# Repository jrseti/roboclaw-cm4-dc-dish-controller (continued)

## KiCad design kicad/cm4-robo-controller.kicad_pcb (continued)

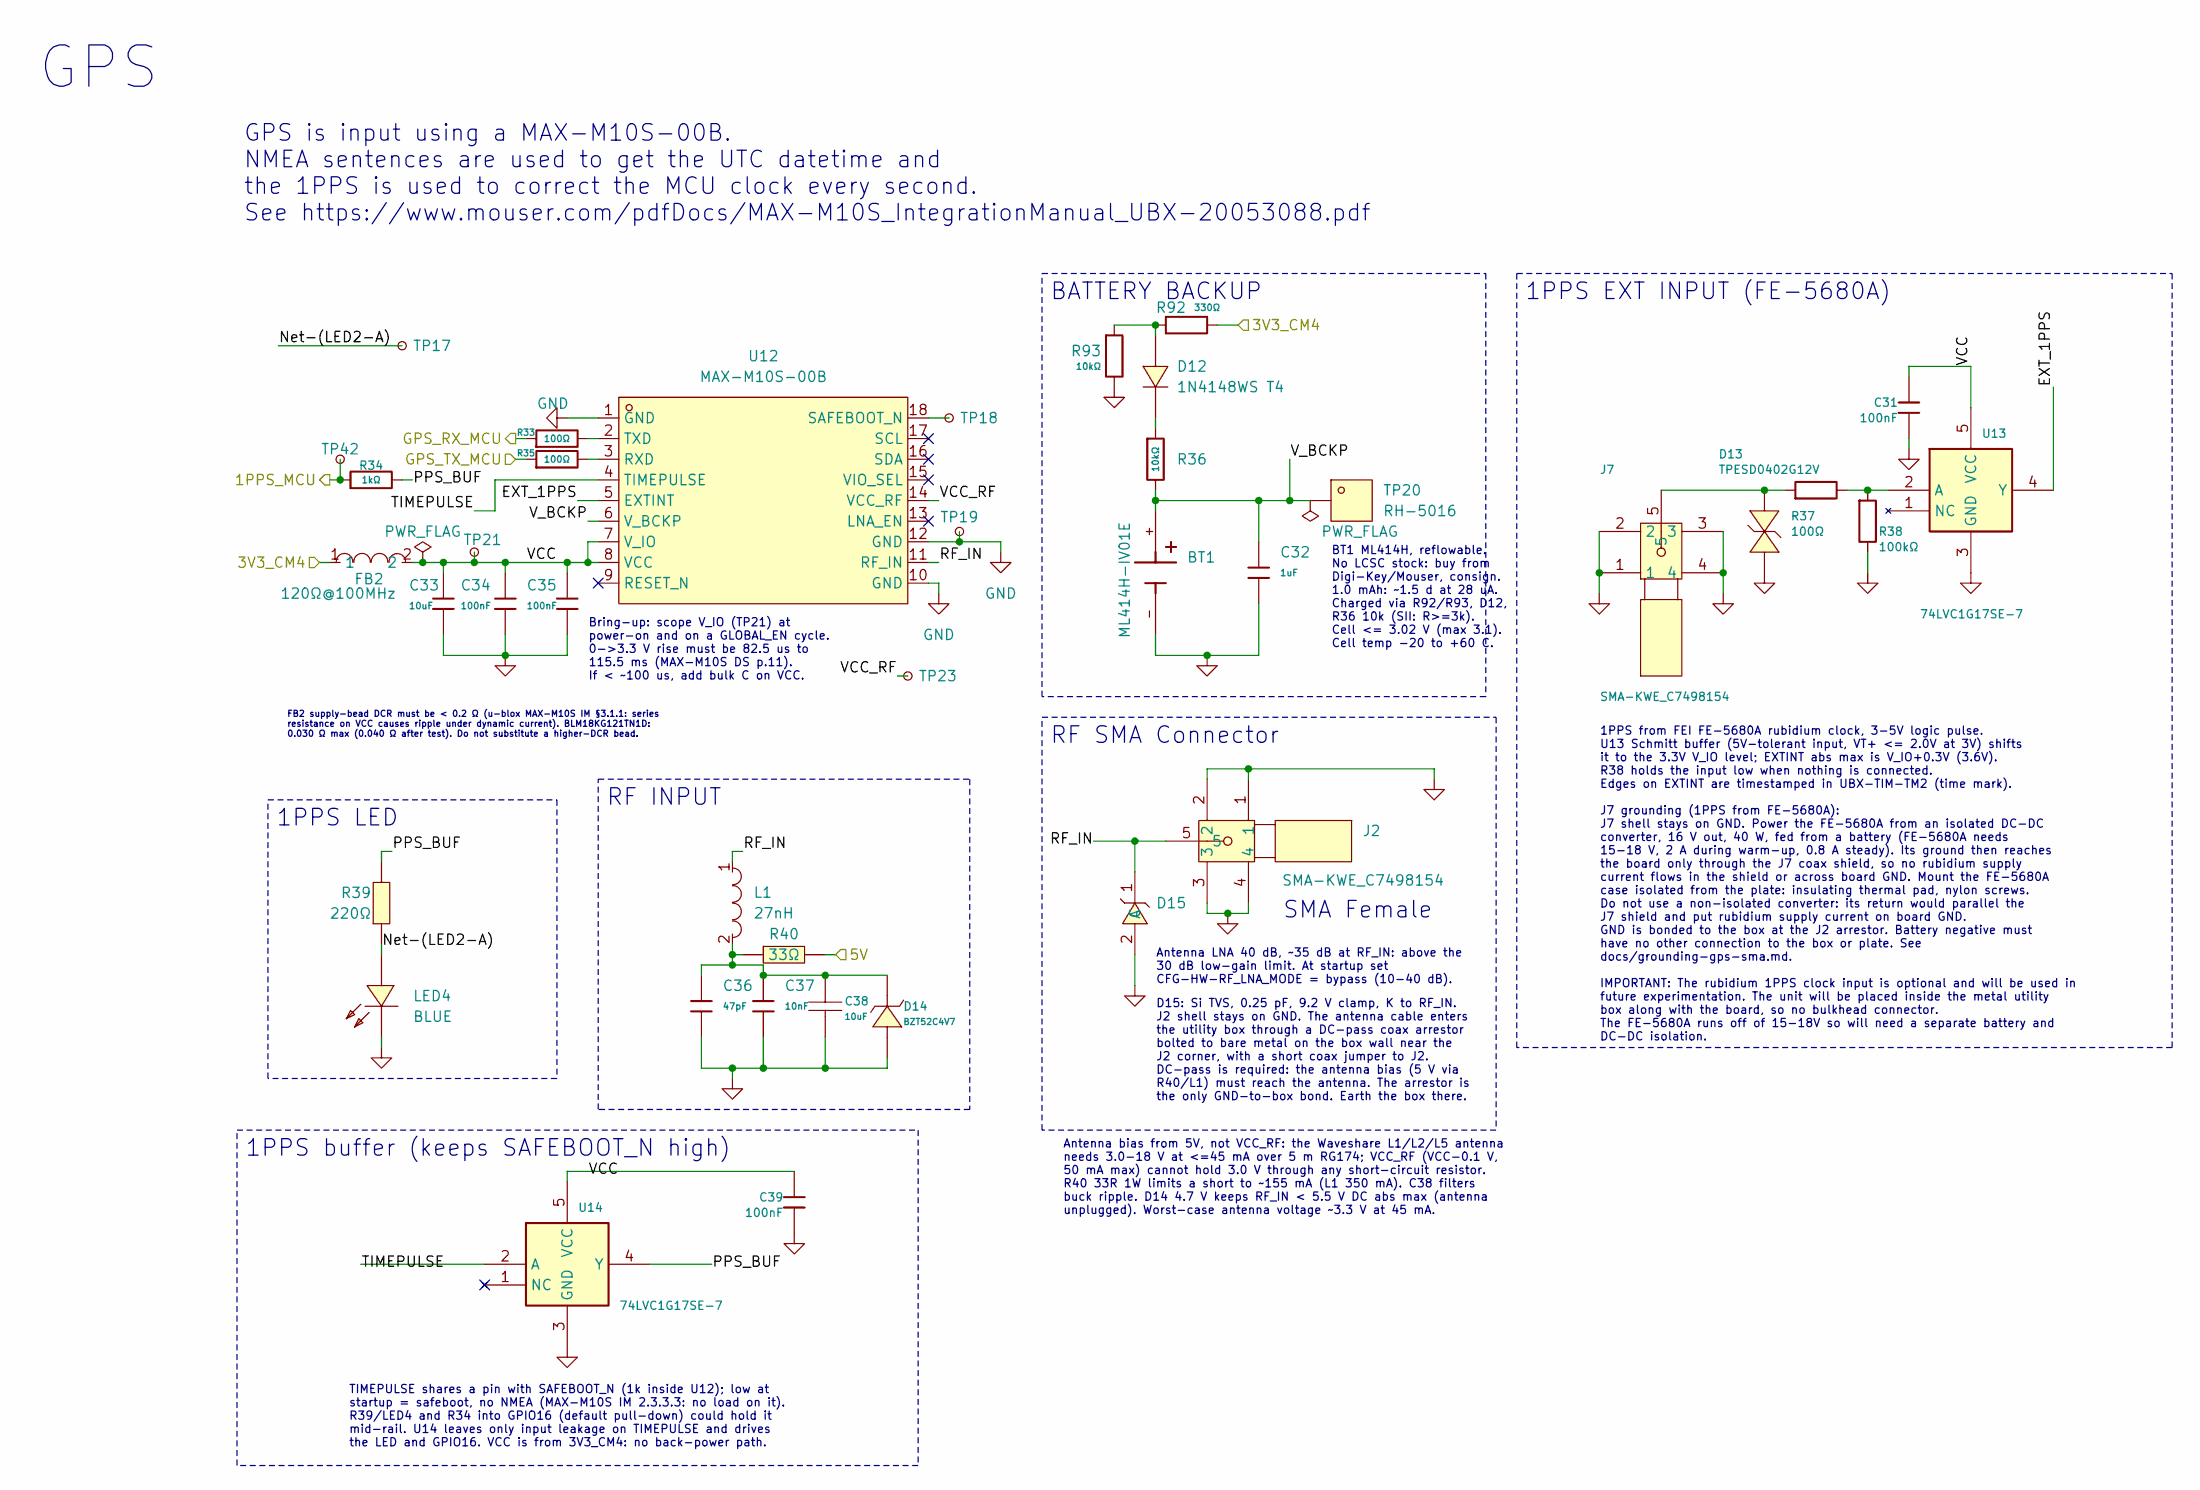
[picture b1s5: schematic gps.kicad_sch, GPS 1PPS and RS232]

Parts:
BT1: ML414H-IV01E; PARTREV E
C31, C34, C35, C39: 100nF; CAPC1608X95N; Tolerance ±10%; Voltage Rating 50V; MPN CC0603KRX7R9BB104; LCSC Part C14663
C32: 1uF; CAPC1608X95N; Tolerance ±10%; Voltage Rating 50V; MPN CL10A105KB8NNNC; LCSC Part C15849
C33: 10uF; CAPC1608X95N; Tolerance ±20%; Voltage Rating 25V; MPN CL10A106MA8NRNC; LCSC Part C96446
C36: 47pF; CAPC1608X95N; Tolerance ±5%; Voltage Rating 50V; MPN CL10C470JB8NNNC; LCSC Part C1671
C37: 10nF; CAPC1608X95N; Tolerance ±10%; Voltage Rating 50V; MPN 0603B103K500NT; LCSC Part C57112
C38: 10uF; CAPC2012X145N; Tolerance ±10%; Voltage Rating 10V; MPN CL21B106KPQNNNE; LCSC Part C32635
D12: 1N4148WS T4; SOD2513X110N; MPN 1N4148WS; LCSC Part C2128
D13: TPESD0402G12V; DIOC1005X55N; MPN TPESD0402G12V; LCSC Part C558617
D14: BZT52C4V7; SOD3716X135N; MPN BZT52C4V7; LCSC Part C19077400
D15: SESD0402X1UN-0020-090; DIOC1006X40N; MPN SESD0402X1UN-0020-090; LCSC Part C1973340
FB2: 120Ω@100MHz; INDC1608X95N; Tolerance ±25%; Current Rating 3A; MPN BLM18KG121TN1D; LCSC Part C85831
J2, J7: SMA-KWE_C7498154; SMA-TH_SMA-KWE_C7498154; MPN SMA-KWE; LCSC Part C7498154
L1: 27nH; INDC1005X55N; Tolerance ±5%; Current Rating 350mA; MPN LQG15HS27NJ02D; LCSC Part C12669
LED4: BLUE; LEDC2012X110N; MPN KT-0805B; LCSC Part C2293
R33, R35, R37: 100Ω; RESC1005X40N; Tolerance ±1%; Voltage Rating 50V; MPN 0402WGF1000TCE; LCSC Part C25076
R34: 1kΩ; RESC1005X40N; Tolerance ±1%; Voltage Rating 50V; MPN 0402WGF1001TCE; LCSC Part C11702
R36, R93: 10kΩ; RESC1608X55N; Tolerance ±1%; Voltage Rating 75V; MPN 0603WAF1002T5E; LCSC Part C25804
R38: 100kΩ; RESC1608X55N; Tolerance ±1%; Voltage Rating 75V; MPN 0603WAF1003T5E; LCSC Part C25803
R39: 220Ω; RESC1005X40N; Tolerance ±1%; Voltage Rating 50V; MPN 0402WGF2200TCE; LCSC Part C25091
R40: 33Ω; RESC6332X70N; Tolerance ±1%; Voltage Rating 200V; MPN 25121WF330JT4E; LCSC Part C53728
R92: 330Ω; RESC1608X55N; Tolerance ±1%; Voltage Rating 75V; MPN 0603WAF3300T5E; LCSC Part C23138
TP17, TP18, TP19, TP21, TP23, TP42: TestPoint_Small; TestPoint_Pad_D0.8mm
TP20: RH-5016; TESTPOINT-SMD_L3.0-W2.0; MPN RH-5016; LCSC Part C5199799
U12: MAX-M10S-00B; SMD-18_L10.1-W9.7-P1.10-TL_SKG09F; MPN MAX-M10S-00B; LCSC Part C4153167
U13, U14: 74LVC1G17SE-7; SOT65P210X110-5N; MPN 74LVC1G17SE-7; LCSC Part C212314

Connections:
/3V3_CM4: FB2.1, R92.2; also elsewhere on the board
/5V: R40.2; also elsewhere on the board
/CM4/1PPS_MCU: R34.1, TP42.1 (1_1); also elsewhere on the board
/CM4/GPS_RX_MCU: R33.1; also elsewhere on the board
/CM4/GPS_TX_MCU: R35.1; also elsewhere on the board
/GPS/EXT_1PPS: U12.5 (EXTINT), U13.4 (Y)
/GPS/Net-(LED2-A): LED4.1 (A), R39.1, TP17.1 (1_1)
/GPS/PPS_BUF: R34.2, R39.2, U14.4 (Y)
/GPS/RF_IN: D15.1 (C), J2.5, L1.1, U12.11 (RF_IN)
/GPS/TIMEPULSE: U12.4 (TIMEPULSE), U14.2 (A)
/GPS/VCC: C31.1, C33.1, C34.1, C35.1, C39.1, FB2.2, TP21.1 (1_1), U12.7 (V_IO), U12.8 (VCC), U13.5 (VCC), U14.5 (VCC)
/GPS/VCC_RF: TP23.1 (1_1), U12.14 (VCC_RF)
/GPS/V_BCKP: BT1.+, C32.1, R36.2, TP20.1 (1_1), U12.6 (V_BCKP)
GND: BT1.-, C31.2, C32.2, C33.2, C34.2, C35.2, C36.2, C37.2, C38.1, C39.2, D13.1 (K), D14.2 (A), D15.2 (A), J2.1, J2.2, J2.3, J2.4, J7.1, J7.2, J7.3, J7.4, LED4.2 (K), R38.2, R93.2, TP19.1 (1_1), U12.1 (GND), U12.10 (GND), U12.12 (GND), U13.3 (GND), U14.3 (GND); also elsewhere on the board
unnamed: D12.2 (A), R92.1, R93.1
unnamed: D12.1 (K), R36.1
unnamed: D13.2 (A), J7.5, R37.1
unnamed: C36.1, C37.1, C38.2, D14.1 (K), L1.2, R40.1
unnamed: R35.2, U12.3 (RXD)
unnamed: TP18.1 (1_1), U12.18 (SAFEBOOT_N)
unnamed: R33.2, U12.2 (TXD)
unnamed: R37.2, R38.1, U13.2 (A)

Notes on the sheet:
GPS
Bring-up: scope V_IO (TP21) at power-on and on a GLOBAL_EN cycle. 0->3.3 V rise must be 82.5 us to 115.5 ms (MAX-M10S DS p.11). If < ~100 us, add bulk C on VCC.
1PPS from FEI FE-5680A rubidium clock, 3-5V logic pulse. U13 Schmitt buffer (5V-tolerant input, VT+ <= 2.0V at 3V) shifts it to the 3.3V V_IO level; EXTINT abs max is V_IO+0.3V (3.6V). R38 holds the input low when nothing is connected. Edges on EXTINT are timestamped in UBX-TIM-TM2 (time mark). J7 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
Antenna bias from 5V, not VCC_RF: the Waveshare L1/L2/L5 antenna needs 3.0-18 V at <=45 mA over 5 m RG174; VCC_RF (VCC-0.1 V, 50 mA max) cannot hold 3.0 V through any short-circuit resistor. R40 33R 1W limits a short to ~155 mA (L1 350 mA). C38 filters buck ripple. D14 4.7 V keeps RF_IN < 5.5 V DC 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
FB2 supply-bead DCR must be < 0.2 Ω (u-blox MAX-M10S IM §3.1.1: series resistance on VCC causes ripple under dynamic current). BLM18KG121TN1D: 0.030 Ω max (0.040 Ω after test). Do not substitute a higher-DCR bead.
D15: Si TVS, 0.25 pF, 9.2 V clamp, K to RF_IN. J2 shell stays on GND. The antenna cable enters the utility box through a DC-pass coax arrestor bolted to bare metal on the box wall near the J2 corner, with a short coax jumper to J2. DC-pass is required: the antenna bias (5 V via R40/L1) must reach t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
GPS is input using a MAX-M10S-00B. NMEA sentences are used to get the UTC datetime and the 1PPS is used to correct the MCU clock every second. See https://www.mouser.com/pdfDocs/MAX-M10S_IntegrationManual_UBX-20053088.pdf
SMA Female
BT1 ML414H, reflowable. No LCSC stock: buy from Digi-Key/Mouser, consign. 1.0 mAh: ~1.5 d at 28 uA. Charged via R92/R93, D12, R36 10k (SII: R>=3k). Cell <= 3.02 V (max 3.1). Cell temp -20 to +60 C.
TIMEPULSE shares a pin with SAFEBOOT_N (1k inside U12); low at startup = safeboot, no NMEA (MAX-M10S IM 2.3.3.3: no load on it). R39/LED4 and R34 into GPIO16 (default pull-down) could hold it mid-rail. U14 leaves only input leakage on TIMEPULSE and drives the LED and GPIO16. VCC is from 3V3_CM4: no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
Antenna LNA 40 dB, ~35 dB at RF_IN: above the 30 dB low-gain limit. At startup set CFG-HW-RF_LNA_MODE = bypass (10-40 dB).
RF SMA Connector
1PPS EXT INPUT (FE-5680A)
1PPS buffer (keeps SAFEBOOT_N high)
1PPS LED
RF INPUT
BATTERY BACKUP

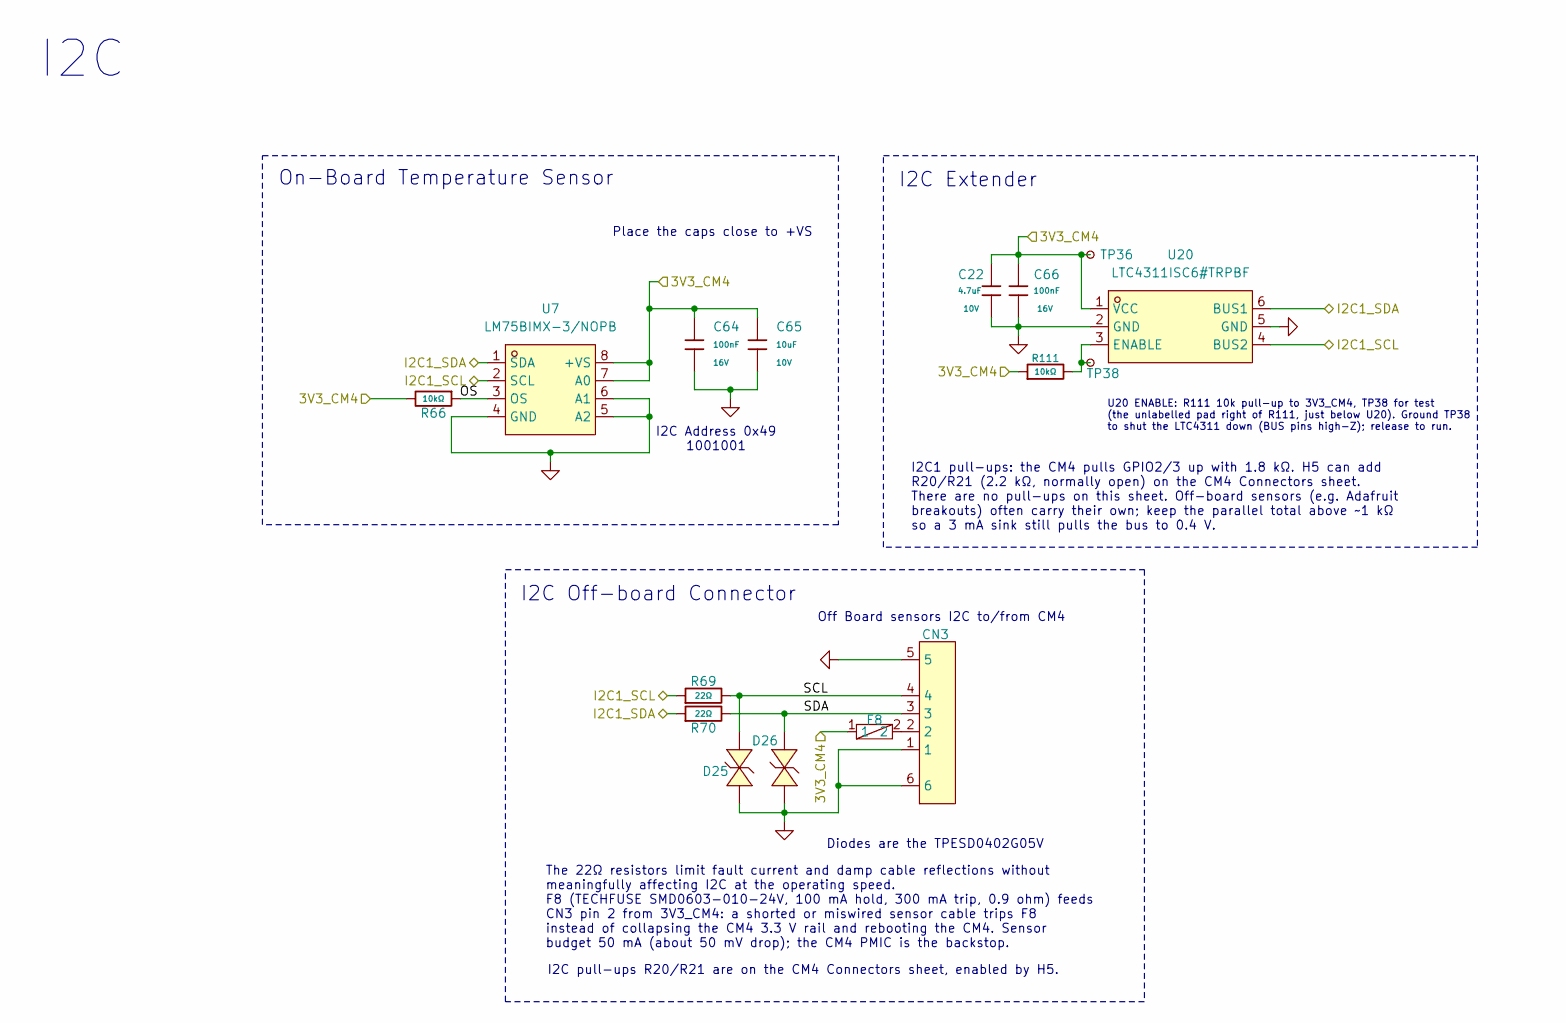
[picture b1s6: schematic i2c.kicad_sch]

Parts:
C22: 4.7uF; CAPC1005X55N; Voltage Rated 10V; Tolerance ±20%; MPN CL05A475MP5NRNC; LCSC Part C23733
C64, C66: 100nF; CAPC1005X55N; Voltage Rated 16V; Tolerance ±10%; MPN CL05B104KO5NNNC; LCSC Part C1525
C65: 10uF; CAPC1608X95N; Voltage Rated 10V; Tolerance ±10%; MPN CL10A106KP8NNNC; LCSC Part C19702
CN3: SM04B-SRSS-TB (LF)(SN); JST_SH_SM04B-SRSS-TB_1x04-1MP_P1.00mm_Horizontal; MPN SM04B-SRSS-TB(LF)(SN); LCSC Part C160404
D25, D26: TPESD0402G05V; DIOC1005X55N; MPN TPESD0402G05V; LCSC Part C558615
F8: 100mA; FUSC1608X100N; MPN SMD0603-010-24V; LCSC Part C70048
R66: 10kΩ; RESC1005X40N; Overload Voltage (Max) 50V; Tolerance ±1%; MPN 0402WGF1002TCE; LCSC Part C25744
R69: 22Ω; RESC1005X40N; Overload Voltage (Max) 50V; Tolerance ±1%; MPN 0402WGF220JTCE; LCSC Part C25092
R70: 22Ω; RESC1005X40N; Overload Voltage (Max) 50V; Tolerance ±1%; Part 0402WGF220JTCE; LCSC Part C25092
R111: 10kΩ; RESC1005X40N; Tolerance ±1%; Voltage Rating 50V; MPN 0402WGF1002TCE; LCSC Part C25744
TP36, TP38: TestPoint_Small; TestPoint_Pad_D0.8mm
U7: LM75BIMX-3/NOPB; SOIC127P600X175-8N; MPN LM75BIMX-3/NOPB; LCSC Part C477980
U20: LTC4311ISC6#TRPBF; SOT65P210X110-6N; MPN LTC4311ISC6#TRPBF; LCSC Part C688097

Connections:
/3V3_CM4: C22.1, C64.1, C65.1, C66.1, F8.1, R66.2, R111.1, TP36.1 (1_1), U7.7 (A0), U7.8 (+VS), U20.1 (VCC); also elsewhere on the board
/CM4/I2C1_SCL: R69.1, U7.2 (SCL), U20.4 (BUS2); also elsewhere on the board
/CM4/I2C1_SDA: R70.1, U7.1 (SDA), U20.6 (BUS1); also elsewhere on the board
/CM4/I2C/OS: R66.1, U7.3 (OS)
/CM4/I2C/SCL: CN3.4, D25.1 (K), R69.2
/CM4/I2C/SDA: CN3.3, D26.1 (K), R70.2
GND: C22.2, C64.2, C65.2, C66.2, CN3.1, CN3.5, CN3.6, D25.2 (A), D26.2 (A), U7.4 (GND), U7.5 (A2), U7.6 (A1), U20.2 (GND), U20.5 (GND); also elsewhere on the board
unnamed: CN3.2, F8.2
unnamed: R111.2, TP38.1 (1_1), U20.3 (ENABLE)

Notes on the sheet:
I2C1 pull-ups: the CM4 pulls GPIO2/3 up with 1.8 kΩ. H5 can add R20/R21 (2.2 kΩ, normally open) on the CM4 Connectors sheet. There are no pull-ups on this sheet. Off-board sensors (e.g. Adafruit breakouts) often carry their own; keep the parallel total above ~1 kΩ so a 3 mA sink still pulls the bus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
I2C pull-ups R20/R21 are on the CM4 Connectors sheet, enabled by H5.
Diodes are the TPESD0402G05V
Place the caps close to +VS
I2C Address 0x49 1001001
I2C
The 22Ω resistors limit fault current and damp cable reflections without meaningfully affecting I2C at the operating speed. F8 (TECHFUSE SMD0603-010-24V, 100 mA hold, 300 mA trip, 0.9 ohm) feeds CN3 pin 2 from 3V3_CM4: a shorted or miswired sensor cable trips F8 instead of collapsing the CM4 3.3 V 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
U20 ENABLE: R111 10k pull-up to 3V3_CM4, TP38 for test (the unlabelled pad right of R111, just below U20). Ground TP38 to shut the LTC4311 down (BUS pins high-Z); release to run.
I2C Extender
I2C Off-board Connector
Off Board sensors I2C to/from CM4
On-Board Temperature Sensor

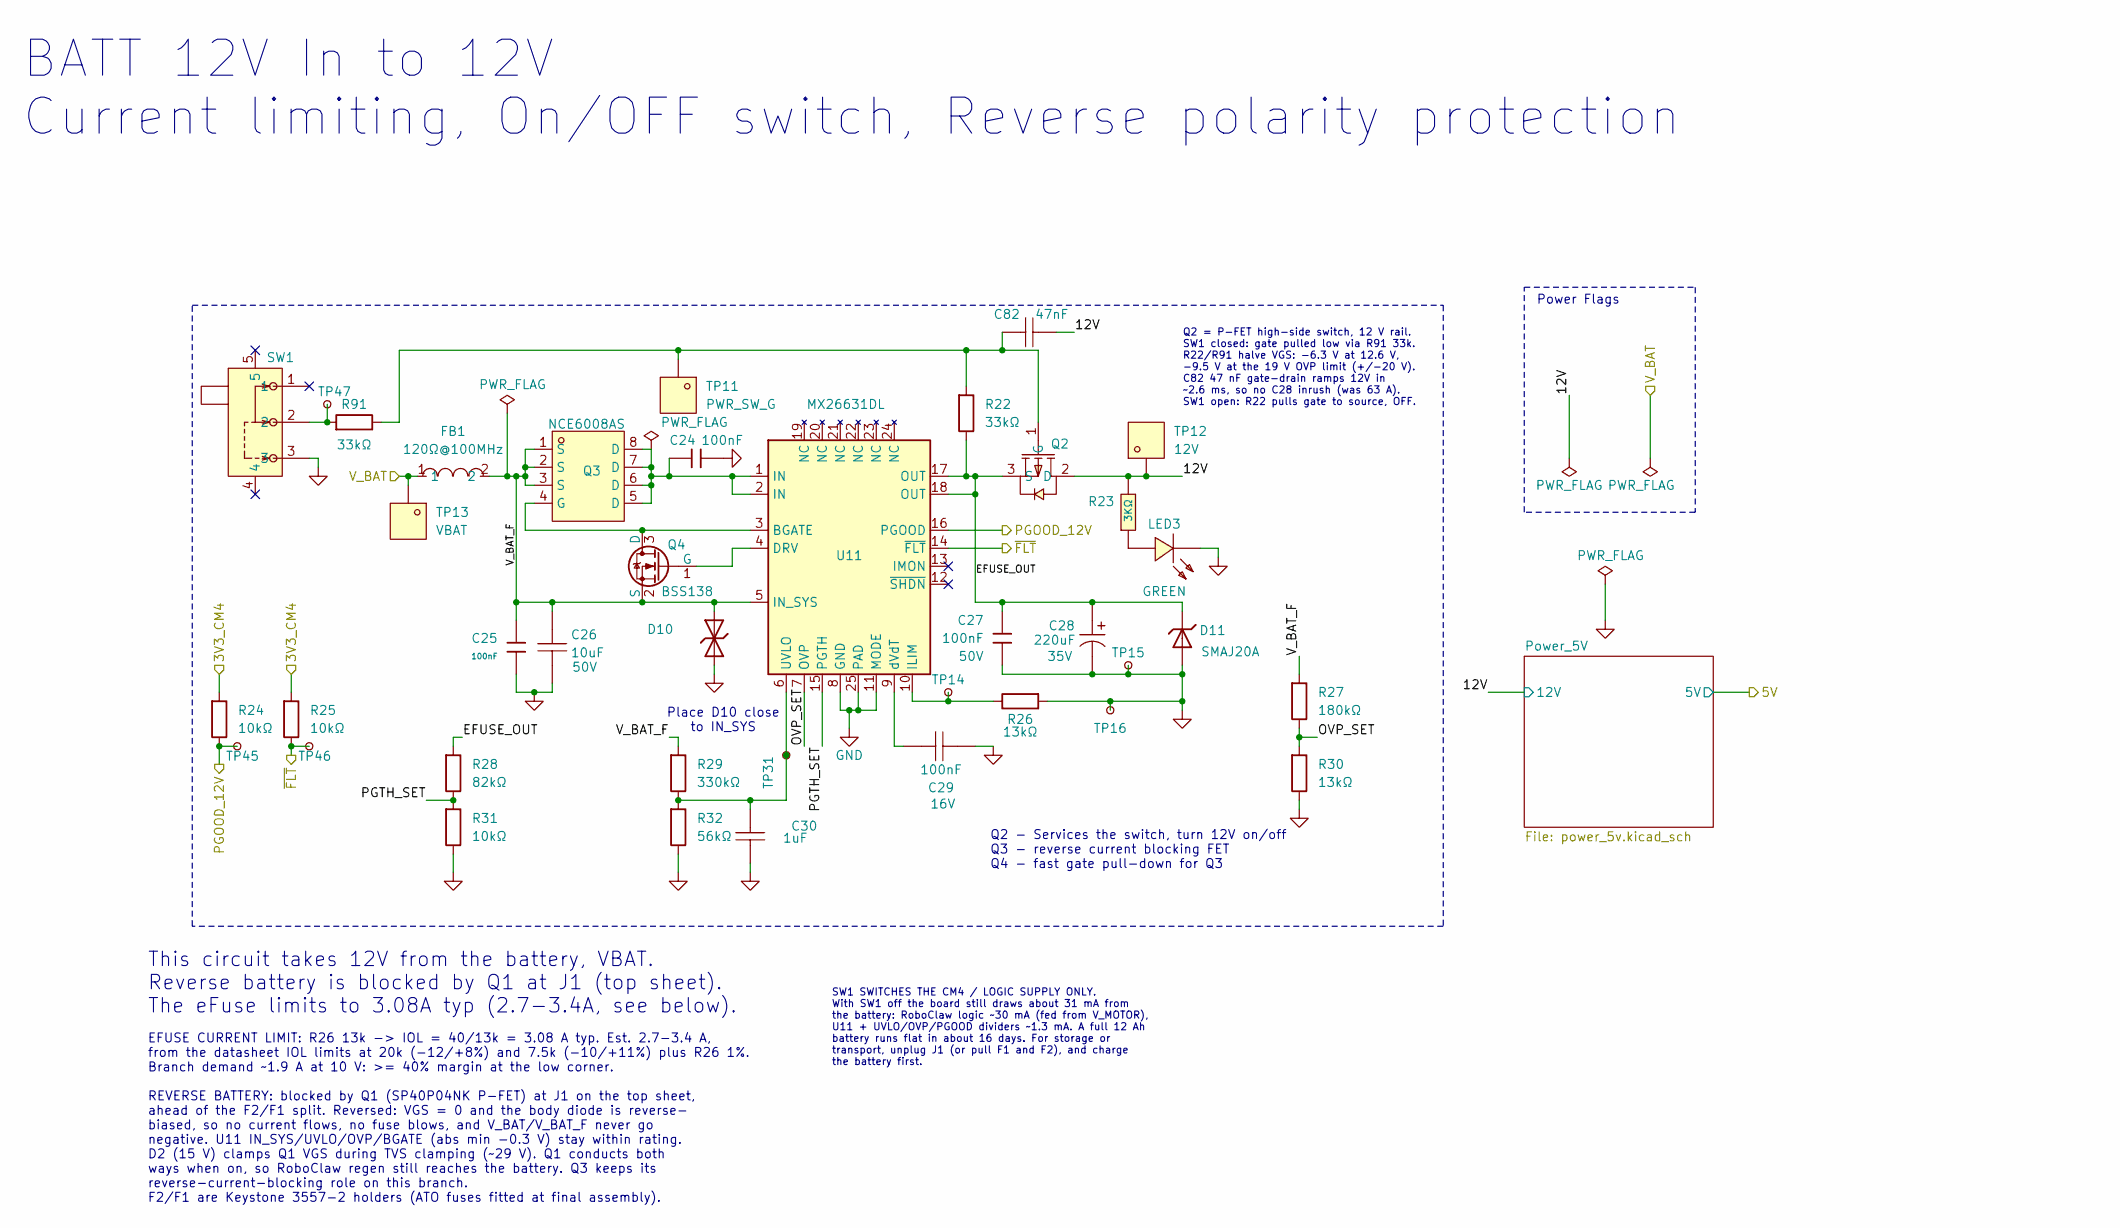
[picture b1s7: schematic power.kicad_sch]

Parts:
C24, C25: 100nF; CAPC1608X95N; Tolerance ±10%; Voltage Rating 50V; MPN CC0603KRX7R9BB104; LCSC Part C14663
C26: 10uF; CAPC3216X180N; Voltage Rating 50V; Tolerance ±10%; MPN TCC1206X7R106K500HT; LCSC Part C5449000
C27: 100nF; CAPC1608X95N; Voltage Rating 50V; Tolerance ±10%; MPN CC0603KRX7R9BB104; LCSC Part C14663
C28: 220uF; CAPAE660X770N; Voltage Rating 35V; Tolerance ±20%; MPN JVJ35V220M6x8; LCSC Part C46550411
C29: 100nF; CAPC1005X55N; Voltage Rating 16V; Tolerance ±10%; MPN CL05B104KO5NNNC; LCSC Part C1525
C30: 1uF; CAPC1608X95N; Tolerance ±10%; Voltage Rating 25V; MPN CL10A105KA8NNNC; LCSC Part C5673
C82: 47nF; CAPC1608X95N; Tolerance ±10%; Voltage Rating 50V; MPN CL10B473KB8NNNC; LCSC Part C1622
D10: SMBJ18CA; DIOM5436X244N; MPN SMBJ18CA; LCSC Part C19077574
D11: SMAJ20A; DIOM5226X244N; MPN SMAJ20A; LCSC Part C41376408
FB1: 120Ω@100MHz; INDC3216X130N; Tolerance ±25%; Current Rating 6A; MPN BLM31KN121SN1L; LCSC Part C337884
LED3: GREEN; LEDC2012X110N; MPN KT-0805G; LCSC Part C2297
Q2: DMP6023LE-13; SOT230P700X180-4N; MPN DMP6023LE-13; LCSC Part C154901
Q3: NCE6008AS; SOIC127P600X175-8N; MPN NCE6008AS; LCSC Part C341716
Q4: BSS138; SOT95P237X112-3N; MPN BSS138; LCSC Part C7420339
R22, R91: 33kΩ; RESC1608X55N; Tolerance ±1%; Voltage Rating 75V; MPN 0603WAF3302T5E; LCSC Part C4216
R23: 3KΩ; RESC1608X55N; Tolerance ±1%; Voltage Rating 75V; MPN 0603WAF3001T5E; LCSC Part C4211
R24, R25, R31: 10kΩ; RESC1608X55N; Tolerance ±1%; Voltage Rating 75V; MPN 0603WAF1002T5E; LCSC Part C25804
R26, R30: 13kΩ; RESC1608X55N; Tolerance ±1%; Voltage Rating 75V; MPN 0603WAF1302T5E; LCSC Part C22797
R27: 180kΩ; RESC1608X55N; Tolerance ±1%; Voltage Rating 75V; MPN 0603WAF1803T5E; LCSC Part C22827
R28: 82kΩ; RESC1608X55N; Tolerance ±1%; Voltage Rating 75V; MPN 0603WAF8202T5E; LCSC Part C23254
R29: 330kΩ; RESC1608X55N; Tolerance ±1%; Voltage Rating 75V; MPN 0603WAF3303T5E; LCSC Part C23137
R32: 56kΩ; RESC1608X55N; Tolerance ±1%; Voltage Rating 75V; MPN 0603WAF5602T5E; LCSC Part C23206
SW1: SS-12F49-G050; SW-TH_SS-12F45-GXXX; MPN SS-12F49-G050; LCSC Part C2876010
TP11: PWR_SW_G; TESTPOINT-SMD_L3.0-W2.0; MPN RH-5016; LCSC Part C5199799
TP12: 12V; TESTPOINT-SMD_L3.0-W2.0; MPN RH-5016; LCSC Part C5199799
TP13: VBAT; TESTPOINT-SMD_L3.0-W2.0; MPN RH-5016; LCSC Part C5199799
TP14, TP15, TP16, TP31, TP45, TP46, TP47: TestPoint_Small; TestPoint_Pad_D0.8mm
U11: MX26631DL; QFN50P400X400X80-25N; MPN MX26631DL; LCSC C18197523

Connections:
/3V3_CM4: R24.1, R25.1; also elsewhere on the board
/CM4/PGOOD_12V: R24.2, TP45.1 (1_1), U11.16 (PGOOD); also elsewhere on the board
/CM4/~FLT: R25.2, TP46.1 (1_1), U11.14 (~FLT); also elsewhere on the board
/battery-input/V_BAT: FB1.1, TP13.1 (1_1); also elsewhere on the board
/power/12V: C82.2, Q2.2 (D), R23.2, TP12.1 (1_1); also elsewhere on the board
/power/EFUSE_OUT: C27.1, C28.1, D11.1, Q2.3 (S), R22.2, R28.1, U11.17 (OUT), U11.18 (OUT)
/power/OVP_SET: R27.2, R30.1, U11.7 (OVP)
/power/PGTH_SET: R28.2, R31.1, U11.15 (PGTH)
/power/V_BAT_F: C25.1, C26.2, D10.1, FB1.2, Q3.1 (S), Q3.2 (S), Q3.3 (S), Q4.2 (S), R27.1, R29.1, U11.5 (IN_SYS)
GND: C24.2, C25.2, C26.1, C27.2, C28.2, C29.2, C30.1, D10.2, D11.2, LED3.2 (K), R26.1, R30.2, R31.2, R32.2, SW1.3, TP15.1 (1_1), TP16.1 (1_1), U11.8 (GND), U11.11 (MODE), U11.25 (PAD); also elsewhere on the board
unnamed: C24.1, Q3.5 (D), Q3.6 (D), Q3.7 (D), Q3.8 (D), U11.1 (IN), U11.2 (IN)
unnamed: LED3.1 (A), R23.1
unnamed: C82.1, Q2.1 (G), R22.1, R91.2, TP11.1 (1_1)
unnamed: Q3.4 (G), Q4.3 (D), U11.3 (BGATE)
unnamed: Q4.1 (G), U11.4 (DRV)
unnamed: R91.1, SW1.2, TP47.1 (1_1)
unnamed: R26.2, TP14.1 (1_1), U11.10 (ILIM)
unnamed: C30.2, R29.2, R32.1, TP31.1 (1_1), U11.6 (UVLO)
unnamed: C29.1, U11.9 (dVdT)

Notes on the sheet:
EFUSE CURRENT LIMIT: R26 13k -> IOL = 40/13k = 3.08 A typ. Est. 2.7-3.4 A, from the datasheet IOL limits at 20k (-12/+8%) and 7.5k (-10/+11%) plus R26 1%. Branch demand ~1.9 A at 10 V: >= 40% margin at the low corner. REVERSE BATTERY: blocked by Q1 (SP40P04NK P-FET) at J1 on the top sheet, ahead of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
BATT 12V In to 12V Current limiting, On/OFF switch, Reverse polarity protection
SW1 SWITCHES THE CM4 / LOGIC SUPPLY ONLY. With SW1 off the board still draws about 31 mA from the battery: RoboClaw logic ~30 mA (fed from V_MOTOR), U11 + UVLO/OVP/PGOOD dividers ~1.3 mA. A full 12 Ah battery runs flat in about 16 days. For storage or transport, unplug J1 (or pull F1 and F2), and c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
Place D10 close to IN_SYS
This circuit takes 12V from the battery, VBAT. Reverse battery is blocked by Q1 at J1 (top sheet). The eFuse limits to 3.08A typ (2.7-3.4A, see below).
Q2 - Services the switch, turn 12V on/off Q3 - reverse current blocking FET Q4 - fast gate pull-down for Q3
Power Flags
Q2 = P-FET high-side switch, 12 V rail. SW1 closed: gate pulled low via R91 33k. R22/R91 halve VGS: -6.3 V at 12.6 V, -9.5 V at the 19 V OVP limit (+/-20 V). C82 47 nF gate-drain ramps 12V in ~2.6 ms, so no C28 inrush (was 63 A). SW1 open: R22 pulls gate to source, OFF.

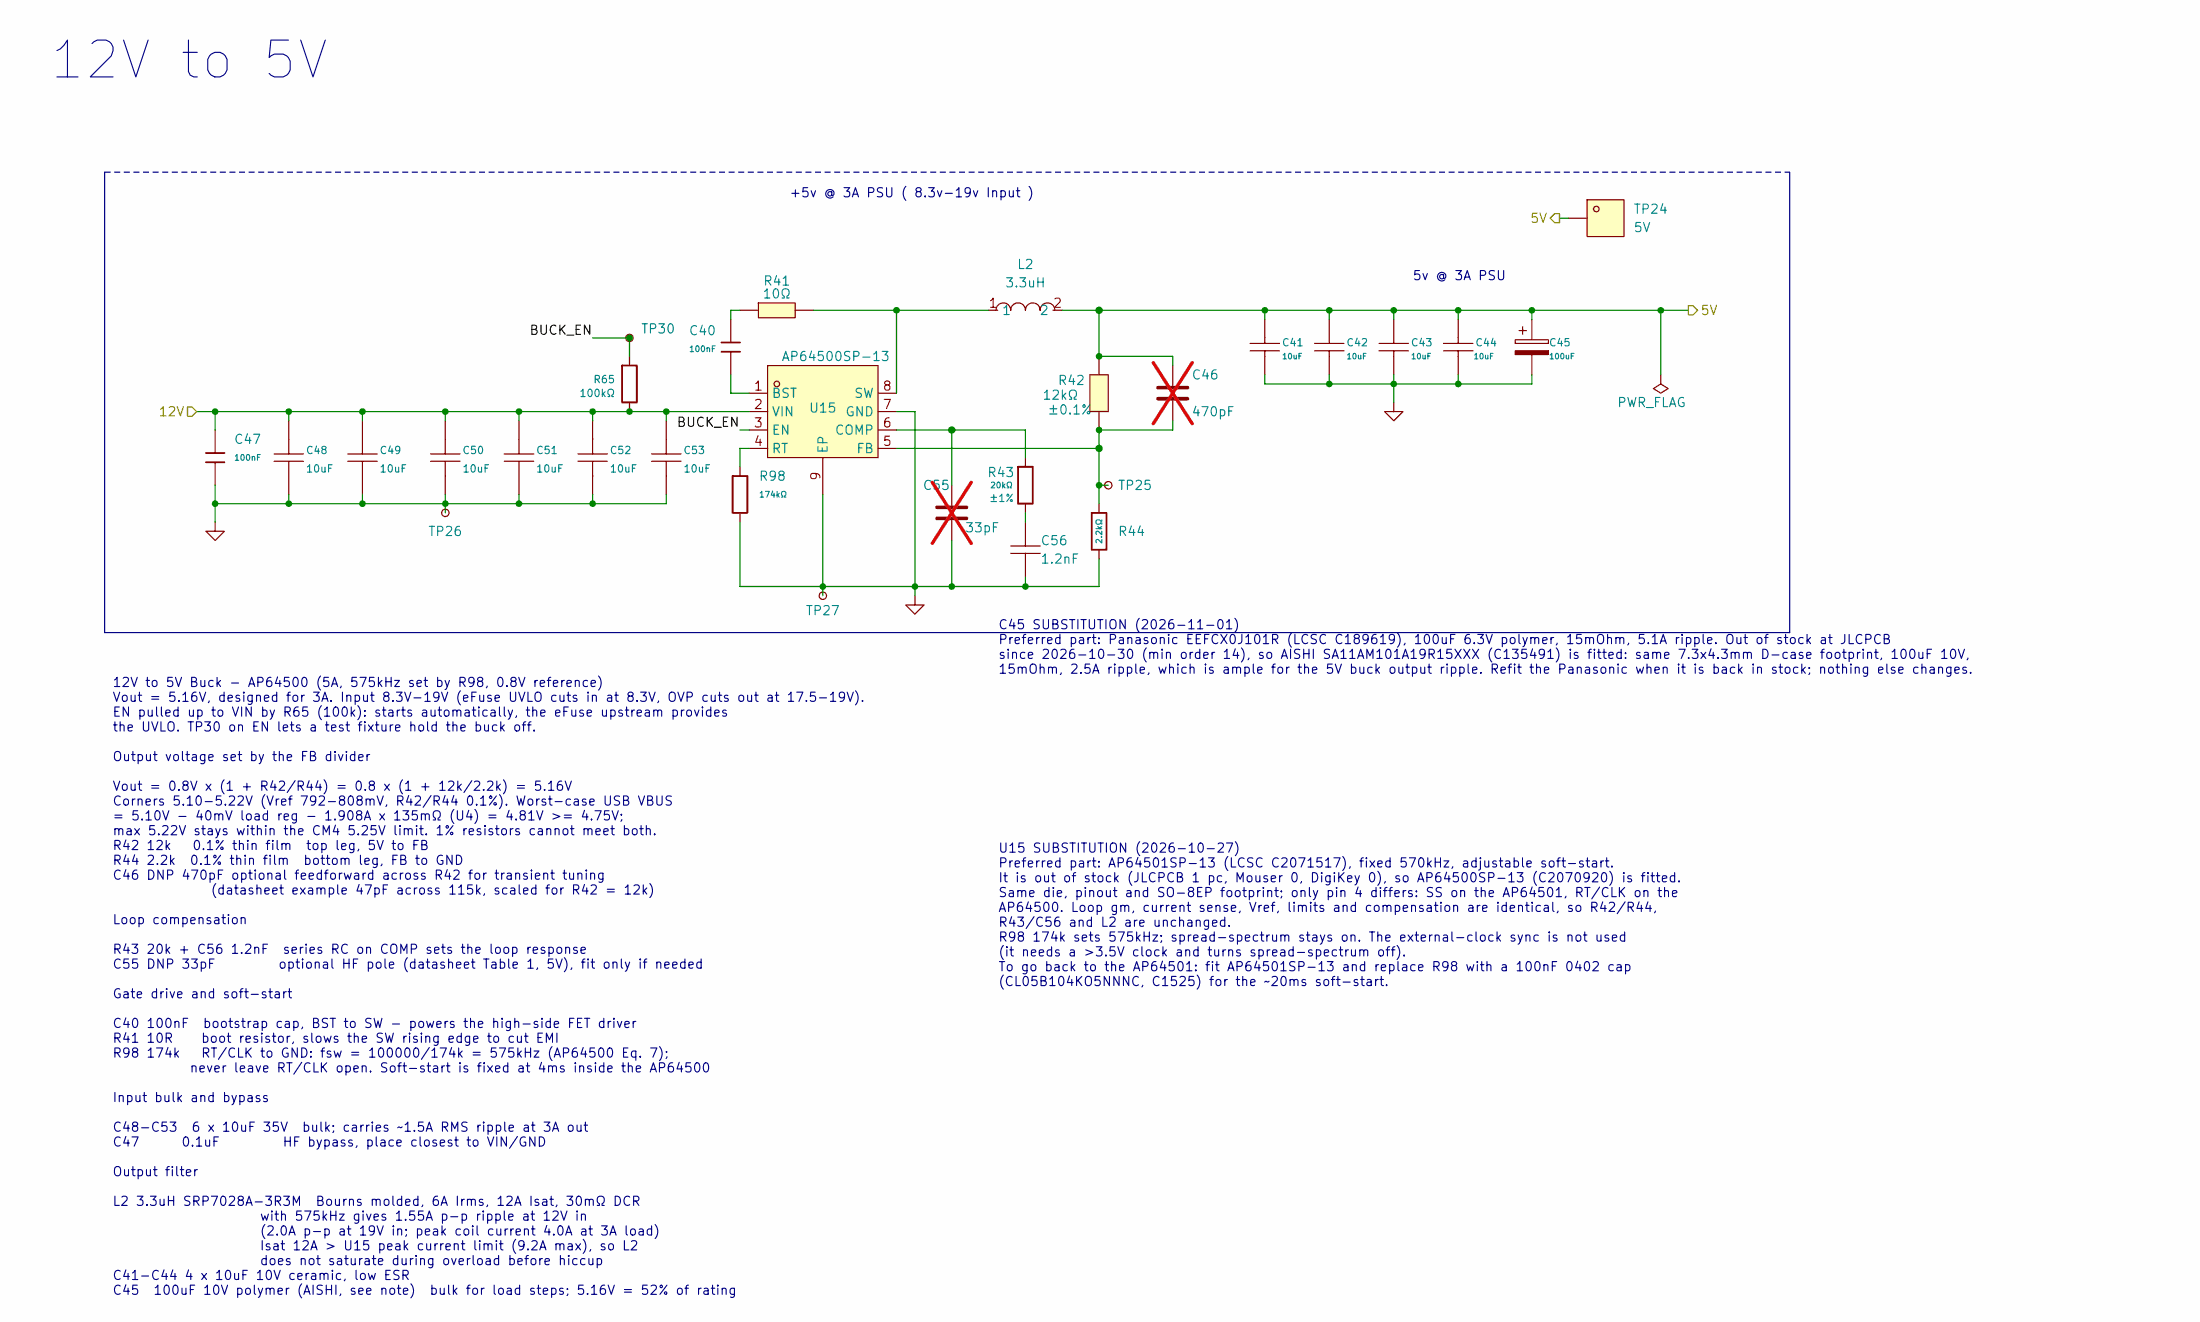
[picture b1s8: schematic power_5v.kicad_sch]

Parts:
C40: 100nF; CAPC1005X55N; Tolerance ±10%; Voltage Rating 16V; MPN CL05B104KO5NNNC; LCSC Part C1525
C41, C42, C43, C44: 10uF; CAPC2012X145N; Tolerance ±10%; Voltage Rating 10V; MPN CL21B106KPQNNNE; LCSC Part C32635
C45: 100uF; CAPMP7343X310N; Tolerance ±20%; Voltage Rating 10V; MPN SA11AM101A19R15XXX; LCSC Part C135491
C46: 470pF; CAPC1005X55N; not fitted
C47: 100nF; CAPC1608X95N; Tolerance ±10%; Voltage Rating 50V; MPN CC0603KRX7R9BB104; LCSC Part C14663
C48, C49, C50, C51, C52, C53: 10uF; CAPC2012X145N; Tolerance ±10%; Voltage Rating 35V; MPN GRM21BC8YA106KE11L; LCSC Part C469541
C55: 33pF; CAPC1005X55N; not fitted
C56: 1.2nF; CAPC1005X55N; Tolerance ±10%; Voltage Rating 50V; MPN CC0402KRX7R9BB122; LCSC Part C107021
L2: 3.3uH; INDM7366X280N; Tolerance ±20%; Current Rating 6A; MPN SRP7028A-3R3M; LCSC Part C913186
R41: 10Ω; RESC3216X70N; Tolerance ±1%; Voltage Rating 200V; MPN 1206W4F100JT5E; LCSC Part C17903
R42: 12kΩ; RESC1005X40N; Tolerance ±0.1%; Voltage Rating 50V; MPN RT0402BRD0712KL; LCSC Part C784579
R43: 20kΩ; RESC1005X40N; Tolerance ±1%; Voltage Rating 50V; MPN 0402WGF2002TCE; LCSC Part C25765
R44: 2.2kΩ; RESC1005X40N; Tolerance ±0.1%; Voltage Rating 50V; MPN RT0402BRD072K2L; LCSC Part C326602
R65: 100kΩ; RESC1005X40N; Tolerance ±1%; Voltage Rating 50V; MPN 0402WGF1003TCE; LCSC Part C25741
R98: 174kΩ; RESC1005X40N; Tolerance ±1%; Voltage Rating 50V; MPN 0402WGF1743TCE; LCSC Part C26994
TP24: 5V; TESTPOINT-SMD_L3.0-W2.0; MPN RH-5016; LCSC Part C5199799
TP25, TP26, TP27, TP30: TestPoint_Small; TestPoint_Pad_D0.8mm
U15: AP64500SP-13; SOIC127P600X170-9N; MPN AP64500SP-13; LCSC Part C2070920

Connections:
/5V: C41.2, C42.2, C43.2, C44.2, C45.1, C46.1, L2.2, R42.2, TP24.1 (1_1); also elsewhere on the board
/power/12V: C47.1, C48.2, C49.2, C50.2, C51.2, C52.2, C53.2, R65.2, U15.2 (VIN); also elsewhere on the board
/power/Power_5V/BUCK_EN: R65.1, TP30.1 (1_1), U15.3 (EN)
GND: C41.1, C42.1, C43.1, C44.1, C45.2, C47.2, C48.1, C49.1, C50.1, C51.1, C52.1, C53.1, C55.2, C56.1, R44.2, R98.2, TP26.1 (1_1), TP27.1 (1_1), U15.7 (GND), U15.9 (EP); also elsewhere on the board
unnamed: C40.1, R41.1
unnamed: C56.2, R43.2
unnamed: C40.2, U15.1 (BST)
unnamed: C55.1, R43.1, U15.6 (COMP)
unnamed: C46.2, R42.1, R44.1, TP25.1 (1_1), U15.5 (FB)
unnamed: R98.1, U15.4 (RT)
unnamed: L2.1, R41.2, U15.8 (SW)

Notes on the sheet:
12V to 5V
5v @ 3A PSU
+5v @ 3A PSU ( 8.3v-19v Input )
U15 SUBSTITUTION (2026-10-27) Preferred part: AP64501SP-13 (LCSC C2071517), fixed 570kHz, adjustable soft-start. It is out of stock (JLCPCB 1 pc, Mouser 0, DigiKey 0), so AP64500SP-13 (C2070920) is fitted. Same die, pinout and SO-8EP footprint; only pin 4 differs: SS on the AP64501, RT/CLK on the A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
12V to 5V Buck - AP64500 (5A, 575kHz set by R98, 0.8V reference) Vout = 5.16V, designed for 3A. Input 8.3V-19V (eFuse UVLO cuts in at 8.3V, OVP cuts out at 17.5-19V). EN pulled up to VIN by R65 (100k): starts automatically, the eFuse upstream provides the UVLO. TP30 on EN lets a test fixture hold t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
C45 SUBSTITUTION (2026-11-01) Preferred part: Panasonic EEFCX0J101R (LCSC C189619), 100uF 6.3V polymer, 15mOhm, 5.1A ripple. Out of stock at JLCPCB since 2026-10-30 (min order 14), so AISHI SA11AM101A19R15XXX (C135491) is fitted: same 7.3x4.3mm D-case footprint, 100uF 10V, 15mOhm, 2.5A ripple, whic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
